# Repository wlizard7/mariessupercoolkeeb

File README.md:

# mariessupercoolkeeb

This is my own personally designed keyboard, mariessupercoolkeeb! It's a keyboard with LED underlighting for each key, 70 keys (woah thats a lot), 2 encoders, and an oled screen. The microcontroller is a raspberry pi pico. I made this because I'm a laptop warrior and want an actual keyboard to plug into my laptop, maybe I'll finally get better at Valorant! (no its a skill issue)

# PCB 

This is the PCB I designed for this keyboard. I added a silkscreen on the back of my favorite character, Iroha from Cosmic Princess Kaguya, on the back to make it feel more like me! The hardest part for me was probably routing... It took me far too long. 

# FIRMWARE

The firmware was made with QMK. I don't know all much about coding but I was able to reverse engineer it using the code from the macro board I made before. 

# Case

I made the case in Fusion360! I'd like to say I'm semi well versed with CAD so it wasn't all that difficult besides the plate which took me a while.

# Final Product

# BOM

| Product | Quantity | Source | Price($) | Link |
| :-----: | :-----: | :-----: | :-----: |  :-----: |
| 3D Printed Case | - | School Printer | - | - |
| Key Stabilizers | 5 | AliExpress | $5.19 | https://a.aliexpress.com/_mPFUoOH |
| Keycaps | 1 | AliExpress | $8.17 | https://a.aliexpress.com/_mLLmu53 |
| Switches | 70 | TikTok Shop | $20.00 | https://www.tiktok.com/t/ZP98jg52vnE6u-AkbOb/ |
| PCB | 1 | JLCPCB | $23.60 | - |
| 1N4148 Diodes | 72 | AliExpress | $23.60 | https://a.aliexpress.com/_mM0KaXP |
| EC11 Rotary Encoder | 1 | AliExpress | $1.58 | https://a.aliexpress.com/_mOKYpCH |
| 0.91 inch OLED display | 1 | AliExpress |$2.37 | https://a.aliexpress.com/_mNspyVF |
| Raspberry Pi Pico | 1 | AliExpress |$3.96| https://a.aliexpress.com/_m0asVHP |
| SK6812 MINI-E | 70 | AliExpress |$3.50 | https://a.aliexpress.com/_m0NRr4N |
| M3 Threaded Inserts | 12 | Have Already | - | - |
| M3 Screws | 12 | Have Already | - | - |

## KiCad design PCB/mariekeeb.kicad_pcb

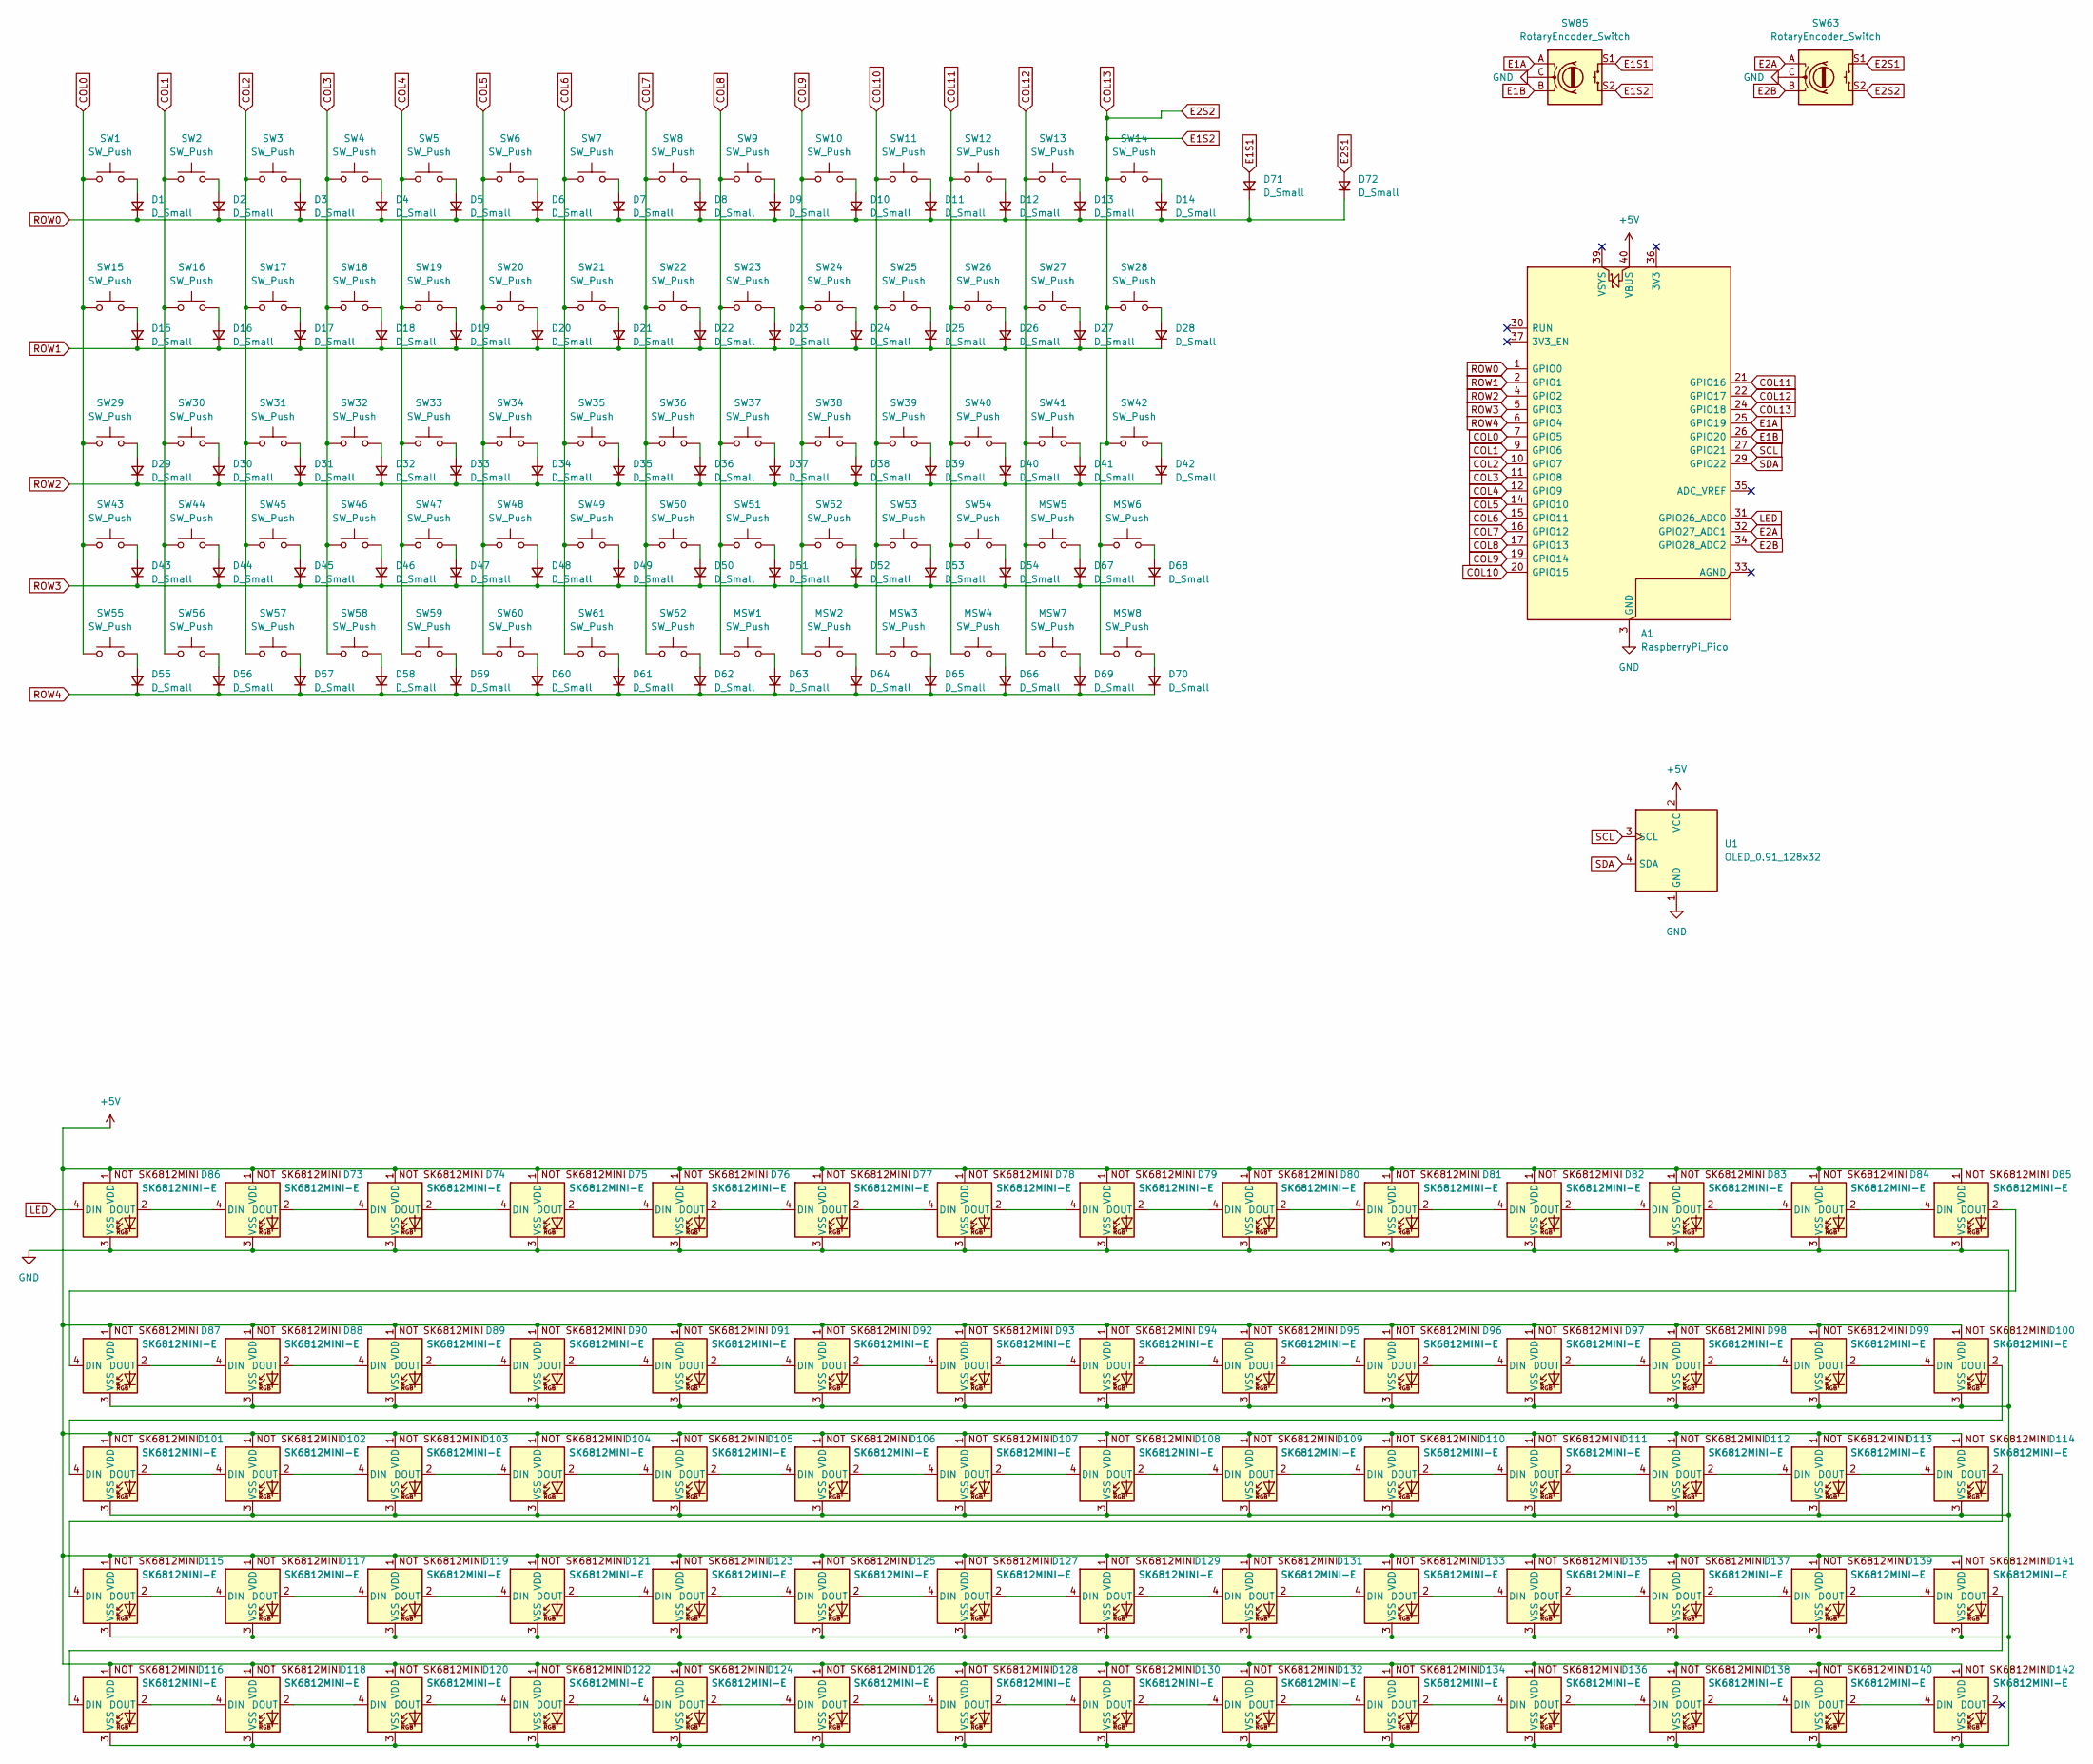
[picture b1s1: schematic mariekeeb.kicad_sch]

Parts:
A1: RaspberryPi_Pico; RaspberryPi_Pico_Common_Unspecified
D1, D2, D3, D4, D5, D6, D7, D8, D9, D10, D11, D12, D13, D14, D15, D16, D17, D18, D19, D20, D21, D22, D23, D24, D25, D26, D27, D28, D29, D30, D31, D32, D33, D34, D35, D36, D37, D38, D39, D40, D41, D42, D43, D44, D45, D46, D47, D48, D49, D50, D51, D52, D53, D54, D55, D56, D57, D58, D59, D60, D61, D62, D63, D64, D65, D66, D67, D68, D69, D70, D71, D72: D_Small; D_DO-35_SOD27_P7.62mm_Horizontal
D73, D74, D75, D76, D77, D78, D79, D80, D81, D82, D83, D84, D85, D86, D87, D88, D89, D90, D91, D92, D93, D94, D95, D96, D97, D98, D99, D100, D101, D102, D103, D104, D105, D106, D107, D108, D109, D110, D111, D112, D113, D114, D115, D116, D117, D118, D119, D120, D121, D122, D123, D124, D125, D126, D127, D128, D129, D130, D131, D132, D133, D134, D135, D136, D137, D138, D139, D140, D141, D142: SK6812MINI-E; MX_SK6812MINI-E_REV
MSW1, MSW2, MSW3, MSW4, MSW5, MSW6, MSW7, MSW8: SW_Push; SW_Cherry_MX_1.00u_PCB
SW1, SW2, SW3, SW4, SW5, SW6, SW7, SW8, SW9, SW10, SW11, SW12, SW13, SW16, SW17, SW18, SW19, SW20, SW21, SW22, SW23, SW24, SW25, SW26, SW27, SW30, SW31, SW32, SW33, SW34, SW35, SW36, SW37, SW38, SW39, SW40, SW44, SW45, SW46, SW47, SW48, SW49, SW50, SW51, SW52, SW53: SW_Push; SW_Cherry_MX_1.00u_PCB
SW14: SW_Push; SW_Cherry_MX_2.00u_PCB
SW15, SW28: SW_Push; SW_Cherry_MX_1.50u_PCB
SW29: SW_Push; SW_Cherry_MX_1.75u_PCB
SW41, SW43: SW_Push; SW_Cherry_MX_2.25u_PCB
SW42: SW_Push; SW_Cherry_MX_2.75u_PCB
SW54, SW55, SW56, SW58, SW59, SW60, SW61, SW62: SW_Push; SW_Cherry_MX_1.25u_PCB
SW57: SW_Push; SW_Cherry_MX_6.25u_PCB
SW63, SW85: RotaryEncoder_Switch; RotaryEncoder_Alps_EC11E-Switch_Vertical_H20mm
U1: OLED_0.91_128x32

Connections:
+5V: A1.40 (VBUS), D73.1 (VDD), D74.1 (VDD), D75.1 (VDD), D76.1 (VDD), D77.1 (VDD), D78.1 (VDD), D79.1 (VDD), D80.1 (VDD), D81.1 (VDD), D82.1 (VDD), D83.1 (VDD), D84.1 (VDD), D85.1 (VDD), D86.1 (VDD), D87.1 (VDD), D88.1 (VDD), D89.1 (VDD), D90.1 (VDD), D91.1 (VDD), D92.1 (VDD), D93.1 (VDD), D94.1 (VDD), D95.1 (VDD), D96.1 (VDD), D97.1 (VDD), D98.1 (VDD), D99.1 (VDD), D100.1 (VDD), D101.1 (VDD), D102.1 (VDD), D103.1 (VDD), D104.1 (VDD), D105.1 (VDD), D106.1 (VDD), D107.1 (VDD), D108.1 (VDD), D109.1 (VDD), D110.1 (VDD), D111.1 (VDD), D112.1 (VDD), D113.1 (VDD), D114.1 (VDD), D115.1 (VDD), D116.1 (VDD), D117.1 (VDD), D118.1 (VDD), D119.1 (VDD), D120.1 (VDD), D121.1 (VDD), D122.1 (VDD), D123.1 (VDD), D124.1 (VDD), D125.1 (VDD), D126.1 (VDD), D127.1 (VDD), D128.1 (VDD), D129.1 (VDD), D130.1 (VDD), D131.1 (VDD), D132.1 (VDD), D133.1 (VDD), D134.1 (VDD), D135.1 (VDD), D136.1 (VDD), D137.1 (VDD), D138.1 (VDD), D139.1 (VDD), D140.1 (VDD), D141.1 (VDD), D142.1 (VDD), U1.2 (VCC)
COL0: A1.7 (GPIO5), SW1.1, SW15.1, SW29.1, SW43.1, SW55.1
COL1: A1.9 (GPIO6), SW2.1, SW16.1, SW30.1, SW44.1, SW56.1
COL2: A1.10 (GPIO7), SW3.1, SW17.1, SW31.1, SW45.1, SW57.1
COL3: A1.11 (GPIO8), SW4.1, SW18.1, SW32.1, SW46.1, SW58.1
COL4: A1.12 (GPIO9), SW5.1, SW19.1, SW33.1, SW47.1, SW59.1
COL5: A1.14 (GPIO10), SW6.1, SW20.1, SW34.1, SW48.1, SW60.1
COL6: A1.15 (GPIO11), SW7.1, SW21.1, SW35.1, SW49.1, SW61.1
COL7: A1.16 (GPIO12), SW8.1, SW22.1, SW36.1, SW50.1, SW62.1
COL8: A1.17 (GPIO13), MSW1.1, SW9.1, SW23.1, SW37.1, SW51.1
COL9: A1.19 (GPIO14), MSW2.1, SW10.1, SW24.1, SW38.1, SW52.1
COL10: A1.20 (GPIO15), MSW3.1, SW11.1, SW25.1, SW39.1, SW53.1
COL11: A1.21 (GPIO16), MSW4.1, SW12.1, SW26.1, SW40.1, SW54.1
COL12: A1.22 (GPIO17), MSW5.1, MSW7.1, SW13.1, SW27.1, SW41.1
COL13: A1.24 (GPIO18), MSW6.1, MSW8.1, SW14.1, SW28.1, SW42.1, SW63.S2, SW85.S2
E1A: A1.25 (GPIO19), SW85.A
E1B: A1.26 (GPIO20), SW85.B
E1S1: D71.2 (A), SW85.S1
E2A: A1.32 (GPIO27_ADC1), SW63.A
E2B: A1.34 (GPIO28_ADC2), SW63.B
E2S1: D72.2 (A), SW63.S1
GND: A1.3 (GND), A1.8 (GND), A1.13 (GND), A1.18 (GND), A1.23 (GND), A1.28 (GND), A1.38 (GND), D73.3 (VSS), D74.3 (VSS), D75.3 (VSS), D76.3 (VSS), D77.3 (VSS), D78.3 (VSS), D79.3 (VSS), D80.3 (VSS), D81.3 (VSS), D82.3 (VSS), D83.3 (VSS), D84.3 (VSS), D85.3 (VSS), D86.3 (VSS), D87.3 (VSS), D88.3 (VSS), D89.3 (VSS), D90.3 (VSS), D91.3 (VSS), D92.3 (VSS), D93.3 (VSS), D94.3 (VSS), D95.3 (VSS), D96.3 (VSS), D97.3 (VSS), D98.3 (VSS), D99.3 (VSS), D100.3 (VSS), D101.3 (VSS), D102.3 (VSS), D103.3 (VSS), D104.3 (VSS), D105.3 (VSS), D106.3 (VSS), D107.3 (VSS), D108.3 (VSS), D109.3 (VSS), D110.3 (VSS), D111.3 (VSS), D112.3 (VSS), D113.3 (VSS), D114.3 (VSS), D115.3 (VSS), D116.3 (VSS), D117.3 (VSS), D118.3 (VSS), D119.3 (VSS), D120.3 (VSS), D121.3 (VSS), D122.3 (VSS), D123.3 (VSS), D124.3 (VSS), D125.3 (VSS), D126.3 (VSS), D127.3 (VSS), D128.3 (VSS), D129.3 (VSS), D130.3 (VSS), D131.3 (VSS), D132.3 (VSS), D133.3 (VSS), D134.3 (VSS), D135.3 (VSS), D136.3 (VSS), D137.3 (VSS), D138.3 (VSS), D139.3 (VSS), D140.3 (VSS), D141.3 (VSS), D142.3 (VSS), SW63.C, SW85.C, U1.1 (GND)
LED: A1.31 (GPIO26_ADC0), D86.4 (DIN)
unnamed: D1.2 (A), SW1.2
unnamed: D2.2 (A), SW2.2
unnamed: D3.2 (A), SW3.2
unnamed: D4.2 (A), SW4.2
unnamed: D5.2 (A), SW5.2
unnamed: D6.2 (A), SW6.2
unnamed: D7.2 (A), SW7.2
unnamed: D8.2 (A), SW8.2
unnamed: D9.2 (A), SW9.2
unnamed: D10.2 (A), SW10.2
unnamed: D11.2 (A), SW11.2
unnamed: D12.2 (A), SW12.2
unnamed: D13.2 (A), SW13.2
unnamed: D14.2 (A), SW14.2
unnamed: D15.2 (A), SW15.2
unnamed: D16.2 (A), SW16.2
unnamed: D17.2 (A), SW17.2
unnamed: D18.2 (A), SW18.2
unnamed: D19.2 (A), SW19.2
unnamed: D20.2 (A), SW20.2
unnamed: D21.2 (A), SW21.2
unnamed: D22.2 (A), SW22.2
unnamed: D23.2 (A), SW23.2
unnamed: D24.2 (A), SW24.2
unnamed: D25.2 (A), SW25.2
unnamed: D26.2 (A), SW26.2
unnamed: D27.2 (A), SW27.2
unnamed: D28.2 (A), SW28.2
unnamed: D29.2 (A), SW29.2
unnamed: D30.2 (A), SW30.2
unnamed: D31.2 (A), SW31.2
unnamed: D32.2 (A), SW32.2
unnamed: D33.2 (A), SW33.2
unnamed: D34.2 (A), SW34.2
unnamed: D35.2 (A), SW35.2
unnamed: D36.2 (A), SW36.2
unnamed: D37.2 (A), SW37.2
unnamed: D38.2 (A), SW38.2
unnamed: D39.2 (A), SW39.2
unnamed: D40.2 (A), SW40.2
unnamed: D41.2 (A), SW41.2
unnamed: D42.2 (A), SW42.2
unnamed: D43.2 (A), SW43.2
unnamed: D44.2 (A), SW44.2
unnamed: D45.2 (A), SW45.2
unnamed: D46.2 (A), SW46.2
unnamed: D47.2 (A), SW47.2
unnamed: D48.2 (A), SW48.2
unnamed: D49.2 (A), SW49.2
unnamed: D50.2 (A), SW50.2
unnamed: D51.2 (A), SW51.2
unnamed: D52.2 (A), SW52.2
unnamed: D53.2 (A), SW53.2
unnamed: D54.2 (A), SW54.2
unnamed: D55.2 (A), SW55.2
unnamed: D56.2 (A), SW56.2
unnamed: D57.2 (A), SW57.2
unnamed: D58.2 (A), SW58.2
unnamed: D59.2 (A), SW59.2
unnamed: D60.2 (A), SW60.2
unnamed: D61.2 (A), SW61.2
unnamed: D62.2 (A), SW62.2
unnamed: D63.2 (A), MSW1.2
unnamed: D64.2 (A), MSW2.2
unnamed: D65.2 (A), MSW3.2
unnamed: D66.2 (A), MSW4.2
unnamed: D67.2 (A), MSW5.2
unnamed: D68.2 (A), MSW6.2
unnamed: D69.2 (A), MSW7.2
unnamed: D70.2 (A), MSW8.2
unnamed: D73.4 (DIN), D86.2 (DOUT)
unnamed: D73.2 (DOUT), D74.4 (DIN)
unnamed: D74.2 (DOUT), D75.4 (DIN)
unnamed: D75.2 (DOUT), D76.4 (DIN)
unnamed: D76.2 (DOUT), D77.4 (DIN)
unnamed: D77.2 (DOUT), D78.4 (DIN)
unnamed: D78.2 (DOUT), D79.4 (DIN)
unnamed: D79.2 (DOUT), D80.4 (DIN)
unnamed: D80.2 (DOUT), D81.4 (DIN)
unnamed: D81.2 (DOUT), D82.4 (DIN)
unnamed: D82.2 (DOUT), D83.4 (DIN)
unnamed: D83.2 (DOUT), D84.4 (DIN)
unnamed: D84.2 (DOUT), D85.4 (DIN)
unnamed: D85.2 (DOUT), D87.4 (DIN)
unnamed: D87.2 (DOUT), D88.4 (DIN)
unnamed: D88.2 (DOUT), D89.4 (DIN)
unnamed: D89.2 (DOUT), D90.4 (DIN)
unnamed: D90.2 (DOUT), D91.4 (DIN)
unnamed: D91.2 (DOUT), D92.4 (DIN)
unnamed: D92.2 (DOUT), D93.4 (DIN)
unnamed: D93.2 (DOUT), D94.4 (DIN)
unnamed: D94.2 (DOUT), D95.4 (DIN)
unnamed: D95.2 (DOUT), D96.4 (DIN)
unnamed: D96.2 (DOUT), D97.4 (DIN)
unnamed: D97.2 (DOUT), D98.4 (DIN)
unnamed: D98.2 (DOUT), D99.4 (DIN)
unnamed: D99.2 (DOUT), D100.4 (DIN)
unnamed: D100.2 (DOUT), D101.4 (DIN)
unnamed: D101.2 (DOUT), D102.4 (DIN)
unnamed: D102.2 (DOUT), D103.4 (DIN)
unnamed: D103.2 (DOUT), D104.4 (DIN)
unnamed: D104.2 (DOUT), D105.4 (DIN)
unnamed: D105.2 (DOUT), D106.4 (DIN)
unnamed: D106.2 (DOUT), D107.4 (DIN)
unnamed: D107.2 (DOUT), D108.4 (DIN)
unnamed: D108.2 (DOUT), D109.4 (DIN)
unnamed: D109.2 (DOUT), D110.4 (DIN)
unnamed: D110.2 (DOUT), D111.4 (DIN)
unnamed: D111.2 (DOUT), D112.4 (DIN)
unnamed: D112.2 (DOUT), D113.4 (DIN)
unnamed: D113.2 (DOUT), D114.4 (DIN)
unnamed: D114.2 (DOUT), D115.4 (DIN)
unnamed: D115.2 (DOUT), D117.4 (DIN)
unnamed: D116.4 (DIN), D141.2 (DOUT)
unnamed: D116.2 (DOUT), D118.4 (DIN)
unnamed: D117.2 (DOUT), D119.4 (DIN)
unnamed: D118.2 (DOUT), D120.4 (DIN)
unnamed: D119.2 (DOUT), D121.4 (DIN)
unnamed: D120.2 (DOUT), D122.4 (DIN)
unnamed: D121.2 (DOUT), D123.4 (DIN)
unnamed: D122.2 (DOUT), D124.4 (DIN)
unnamed: D123.2 (DOUT), D125.4 (DIN)
unnamed: D124.2 (DOUT), D126.4 (DIN)
unnamed: D125.2 (DOUT), D127.4 (DIN)
unnamed: D126.2 (DOUT), D128.4 (DIN)
unnamed: D127.2 (DOUT), D129.4 (DIN)
unnamed: D128.2 (DOUT), D130.4 (DIN)
unnamed: D129.2 (DOUT), D131.4 (DIN)
unnamed: D130.2 (DOUT), D132.4 (DIN)
unnamed: D131.2 (DOUT), D133.4 (DIN)
unnamed: D132.2 (DOUT), D134.4 (DIN)
unnamed: D133.2 (DOUT), D135.4 (DIN)
unnamed: D134.2 (DOUT), D136.4 (DIN)
unnamed: D135.2 (DOUT), D137.4 (DIN)
unnamed: D136.2 (DOUT), D138.4 (DIN)
unnamed: D137.2 (DOUT), D139.4 (DIN)
unnamed: D138.2 (DOUT), D140.4 (DIN)
unnamed: D139.2 (DOUT), D141.4 (DIN)
unnamed: D140.2 (DOUT), D142.4 (DIN)
ROW0: A1.1 (GPIO0), D1.1 (K), D2.1 (K), D3.1 (K), D4.1 (K), D5.1 (K), D6.1 (K), D7.1 (K), D8.1 (K), D9.1 (K), D10.1 (K), D11.1 (K), D12.1 (K), D13.1 (K), D14.1 (K), D71.1 (K), D72.1 (K)
ROW1: A1.2 (GPIO1), D15.1 (K), D16.1 (K), D17.1 (K), D18.1 (K), D19.1 (K), D20.1 (K), D21.1 (K), D22.1 (K), D23.1 (K), D24.1 (K), D25.1 (K), D26.1 (K), D27.1 (K), D28.1 (K)
ROW2: A1.4 (GPIO2), D29.1 (K), D30.1 (K), D31.1 (K), D32.1 (K), D33.1 (K), D34.1 (K), D35.1 (K), D36.1 (K), D37.1 (K), D38.1 (K), D39.1 (K), D40.1 (K), D41.1 (K), D42.1 (K)
ROW3: A1.5 (GPIO3), D43.1 (K), D44.1 (K), D45.1 (K), D46.1 (K), D47.1 (K), D48.1 (K), D49.1 (K), D50.1 (K), D51.1 (K), D52.1 (K), D53.1 (K), D54.1 (K), D67.1 (K), D68.1 (K)
ROW4: A1.6 (GPIO4), D55.1 (K), D56.1 (K), D57.1 (K), D58.1 (K), D59.1 (K), D60.1 (K), D61.1 (K), D62.1 (K), D63.1 (K), D64.1 (K), D65.1 (K), D66.1 (K), D69.1 (K), D70.1 (K)
SCL: A1.27 (GPIO21), U1.3 (SCL)
SDA: A1.29 (GPIO22), U1.4 (SDA)

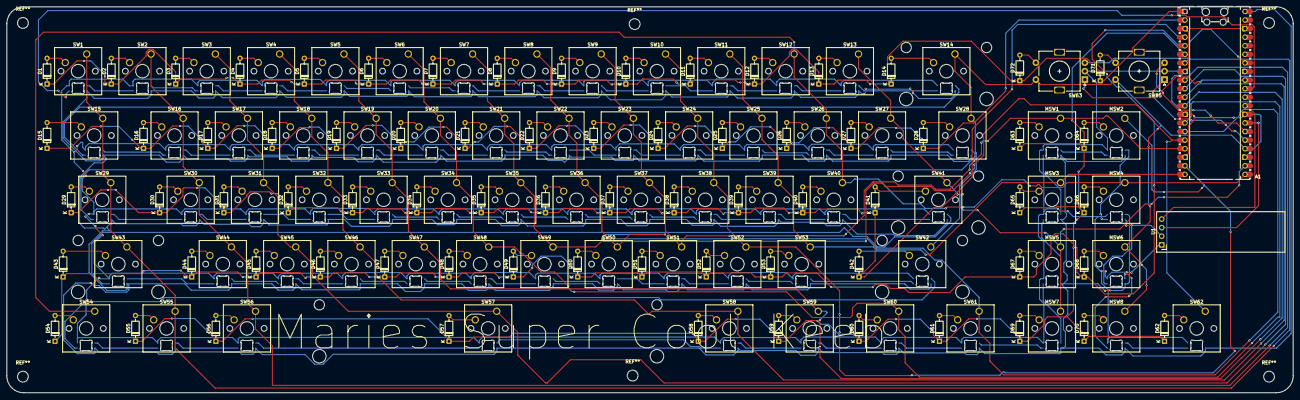
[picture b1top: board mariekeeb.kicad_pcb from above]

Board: 2 copper layers, 381.0 x 114.3 mm, 216 parts (0 on the bottom side), 169 nets.

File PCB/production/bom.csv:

Designator,Footprint,Quantity,Value,LCSC Part #
A1,RaspberryPi_Pico_Common_Unspecified,1,RaspberryPi_Pico,
"D1, D10, D11, D12, D13, D14, D15, D16, D17, D18, D19, D2, D20, D21, D22, D23, D24, D25, D26, D27, D28, D29, D3, D30, D31, D32, D33, D34, D35, D36, D37, D38, D39, D4, D40, D41, D42, D43, D44, D45, D46, D47, D48, D49, D5, D50, D51, D52, D53, D54, D55, D56, D57, D58, D59, D6, D60, D61, D62, D63, D64, D65, D66, D67, D68, D69, D7, D70, D71, D72, D8, D9",D_DO-35_SOD27_P7.62mm_Horizontal,72,D_Small,
"D100, D101, D102, D103, D104, D105, D106, D107, D108, D109, D110, D111, D112, D113, D114, D115, D116, D117, D118, D119, D120, D121, D122, D123, D124, D125, D126, D127, D128, D129, D130, D131, D132, D133, D134, D135, D136, D137, D138, D139, D140, D141, D142, D73, D74, D75, D76, D77, D78, D79, D80, D81, D82, D83, D84, D85, D86, D87, D88, D89, D90, D91, D92, D93, D94, D95, D96, D97, D98, D99",MX_SK6812MINI-E_REV,70,SK6812MINI-E,
"MSW1, MSW2, MSW3, MSW4, MSW5, MSW6, MSW7, MSW8, SW1, SW10, SW11, SW12, SW13, SW16, SW17, SW18, SW19, SW2, SW20, SW21, SW22, SW23, SW24, SW25, SW26, SW27, SW3, SW30, SW31, SW32, SW33, SW34, SW35, SW36, SW37, SW38, SW39, SW4, SW40, SW44, SW45, SW46, SW47, SW48, SW49, SW5, SW50, SW51, SW52, SW53, SW6, SW7, SW8, SW9",SW_Cherry_MX_1.00u_PCB,54,SW_Push,
SW14,SW_Cherry_MX_2.00u_PCB,1,SW_Push,
"SW15, SW28",SW_Cherry_MX_1.50u_PCB,2,SW_Push,
SW29,SW_Cherry_MX_1.75u_PCB,1,SW_Push,
"SW41, SW43",SW_Cherry_MX_2.25u_PCB,2,SW_Push,
SW42,SW_Cherry_MX_2.75u_PCB,1,SW_Push,
"SW54, SW55, SW56, SW58, SW59, SW60, SW61, SW62",SW_Cherry_MX_1.25u_PCB,8,SW_Push,
SW57,SW_Cherry_MX_6.25u_PCB,1,SW_Push,
"SW63, SW85",RotaryEncoder_Alps_EC11E-Switch_Vertical_H20mm,2,RotaryEncoder_Switch,
U1,OLED_0.91_128x32,1,OLED_0.91_128x32,

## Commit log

2026-03-30 Keyboard Firmware
2026-04-04 PCB Files
